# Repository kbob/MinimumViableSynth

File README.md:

# MinimumViableSynth

A virtual analog synthesizer with lots of knobs and buttons.

This is a polyphonic, monotimbral, virtual analog synth.  The audio
engine runs as an Apple Audio Unit on a Macintosh.  The control panel,
shown here, will provide dedicated controls for most of the synth's
functions.

The end goal is a self contained keyboard synth with knobs and buttons
with the classic connections: audio out, MIDI in/out, USB MIDI in/out.
I am getting there in three phases.

  * **Phase 1** (complete 2015-01-01): Softsynth.  The audio engine
    runs as an Audio Unit on a Mac.  It accepts MIDI messages and
    produces beautiful polyphonic analog sounds.  Or gritty,
    disturbing analog sounds.  It plugs in to DAW software (I use
    Logic Pro X).
    
  * **Phase 2** (in progress): Knobs and buttons.  I am designing and
    building a front panel (see above) with knobs, buttons, and an LCD
    touchscreen.  The goal is to make it as easy as possible to
    understand what the synth is doing at any time.

  * **Phase 3** (future): Stand-alone.  Build an enclosure that houses
    a keyboard, the knob and button panel, I/O jacks, and a processor
    (TBD) that can run the audio engine.  I'm looking at FPGAs...

## Why?

Learn stuff.  Music theory, DSP, PCB layout, CAD and machining, more.

## Status

Check out synth-notes.txt for my thoughts as I worked things out.

#### January 7, 2017:

I built 8 slave modules: the LFOs, the Controllers module, the
oscillators, the noise source, mixer, and filter.  I've since killed
the filter module, and one of the oscillators' LED has burnt out its
red component.  I have parts and tools to repair those; just haven't
done it yet.

I have working UI for the knobs and buttons.  Specifically, routing
between modulators and targets works, complete with lighting effects.

I made an enclosure from aluminum sheet and melamine end blocks, as
illustrated above.  It is flimsy, though, so that needs to be re-done.

I had the master, slaves, and LCD panel connected via a breadboard.
The breadboard wiring got flaky, so I stopped to design a PCB.  The
PCB snaps onto the back of the Discovery board, It routes video to the
LCD touch screen, SPI to the slaves, and serial MIDI to a future MIDI
I/O board.

I am currently designing the graphics for the LCD panel.

(Over a year since the last update.  Oops.)

#### December 17, 2015:

Three slave modules have been built.  (LFO1, LFO2, Controllers.)  All
the slave module PCBs are fabricated.

The master-slave communications are working over SPI.  The master
generates MIDI events.
[I can push a button on a slave and hear its effect on the audio
engine.](https://www.youtube.com/watch?v=dZsXk2Zf6Bg)

I blew up one of the LFO modules, probably with static discharge.  I
repaired it (swapped in a new Teensy LC), and it works now.  It was an
ugly repair.

Current tasks:

  + generating more MIDI events
  + experimenting with the LED animation
  + soldering up the rest of the slave modules
  + designing backing plates for the new slave modules

#### August 14, 2015:

The audio engine has been stable since January, though it does not
exactly match the front panel's feature set.

The front panel was fabricated in July.  I used a sheet of acrylic,
painted the underside black, then engraved the artwork through the
paint with a laser cutter.  Then the same laser cutter cut all the
holes for the controls.  It looks sharp, but not mass produced.
I got the work done at [InHaus Fabrication](http://inhausfabrication.com/).

There is a master microcontroller, an STM32F429, and each module has a
slave controller, a Teensy-LC.  Each slave directly drives a few
knobs, buttons, and LEDs.  The master will coordinate all the slaves
and provide the MIDI over USB interface.  I am currently writing SPI
drivers for master-slave communication.

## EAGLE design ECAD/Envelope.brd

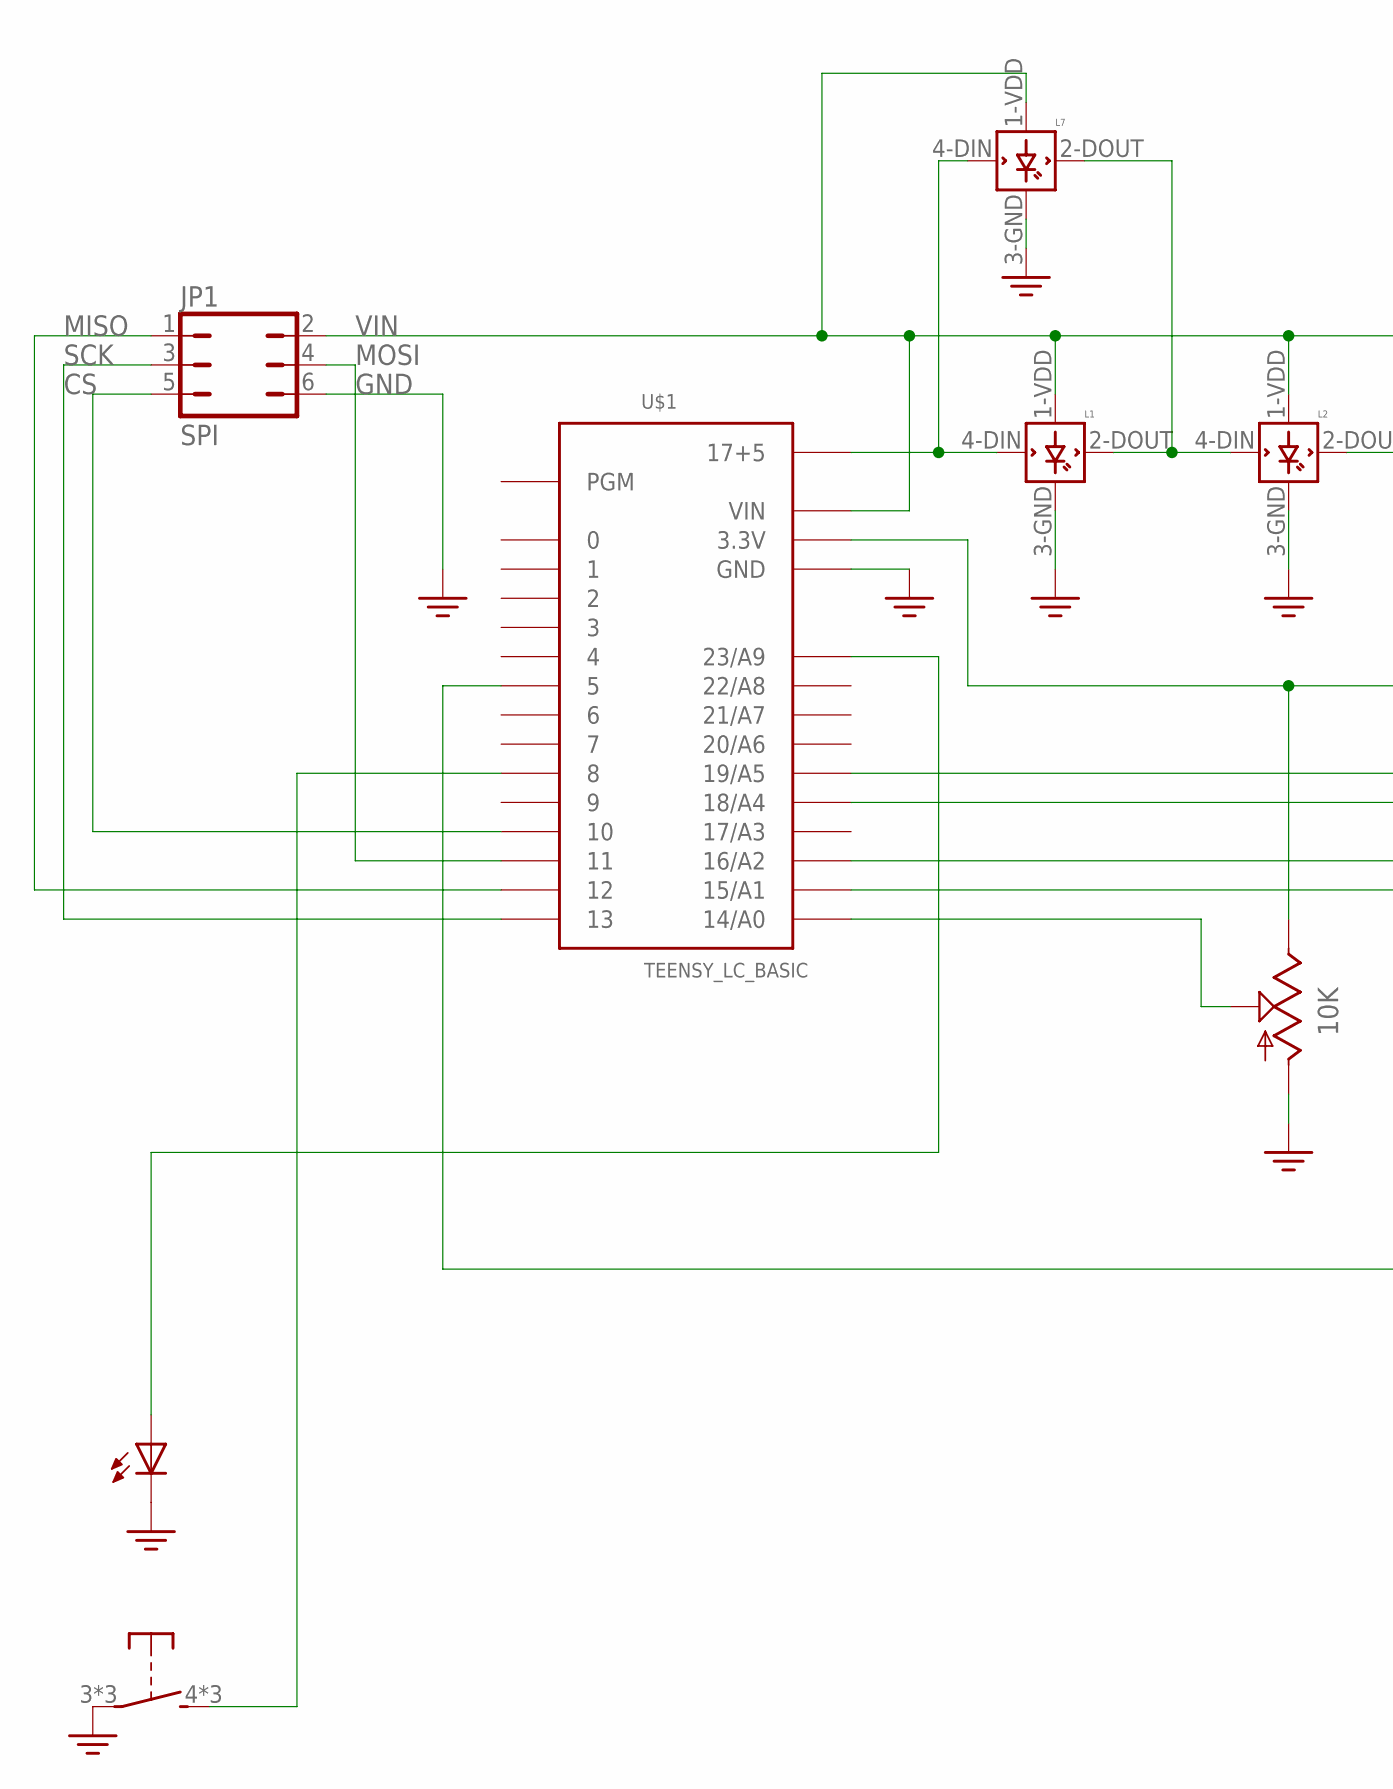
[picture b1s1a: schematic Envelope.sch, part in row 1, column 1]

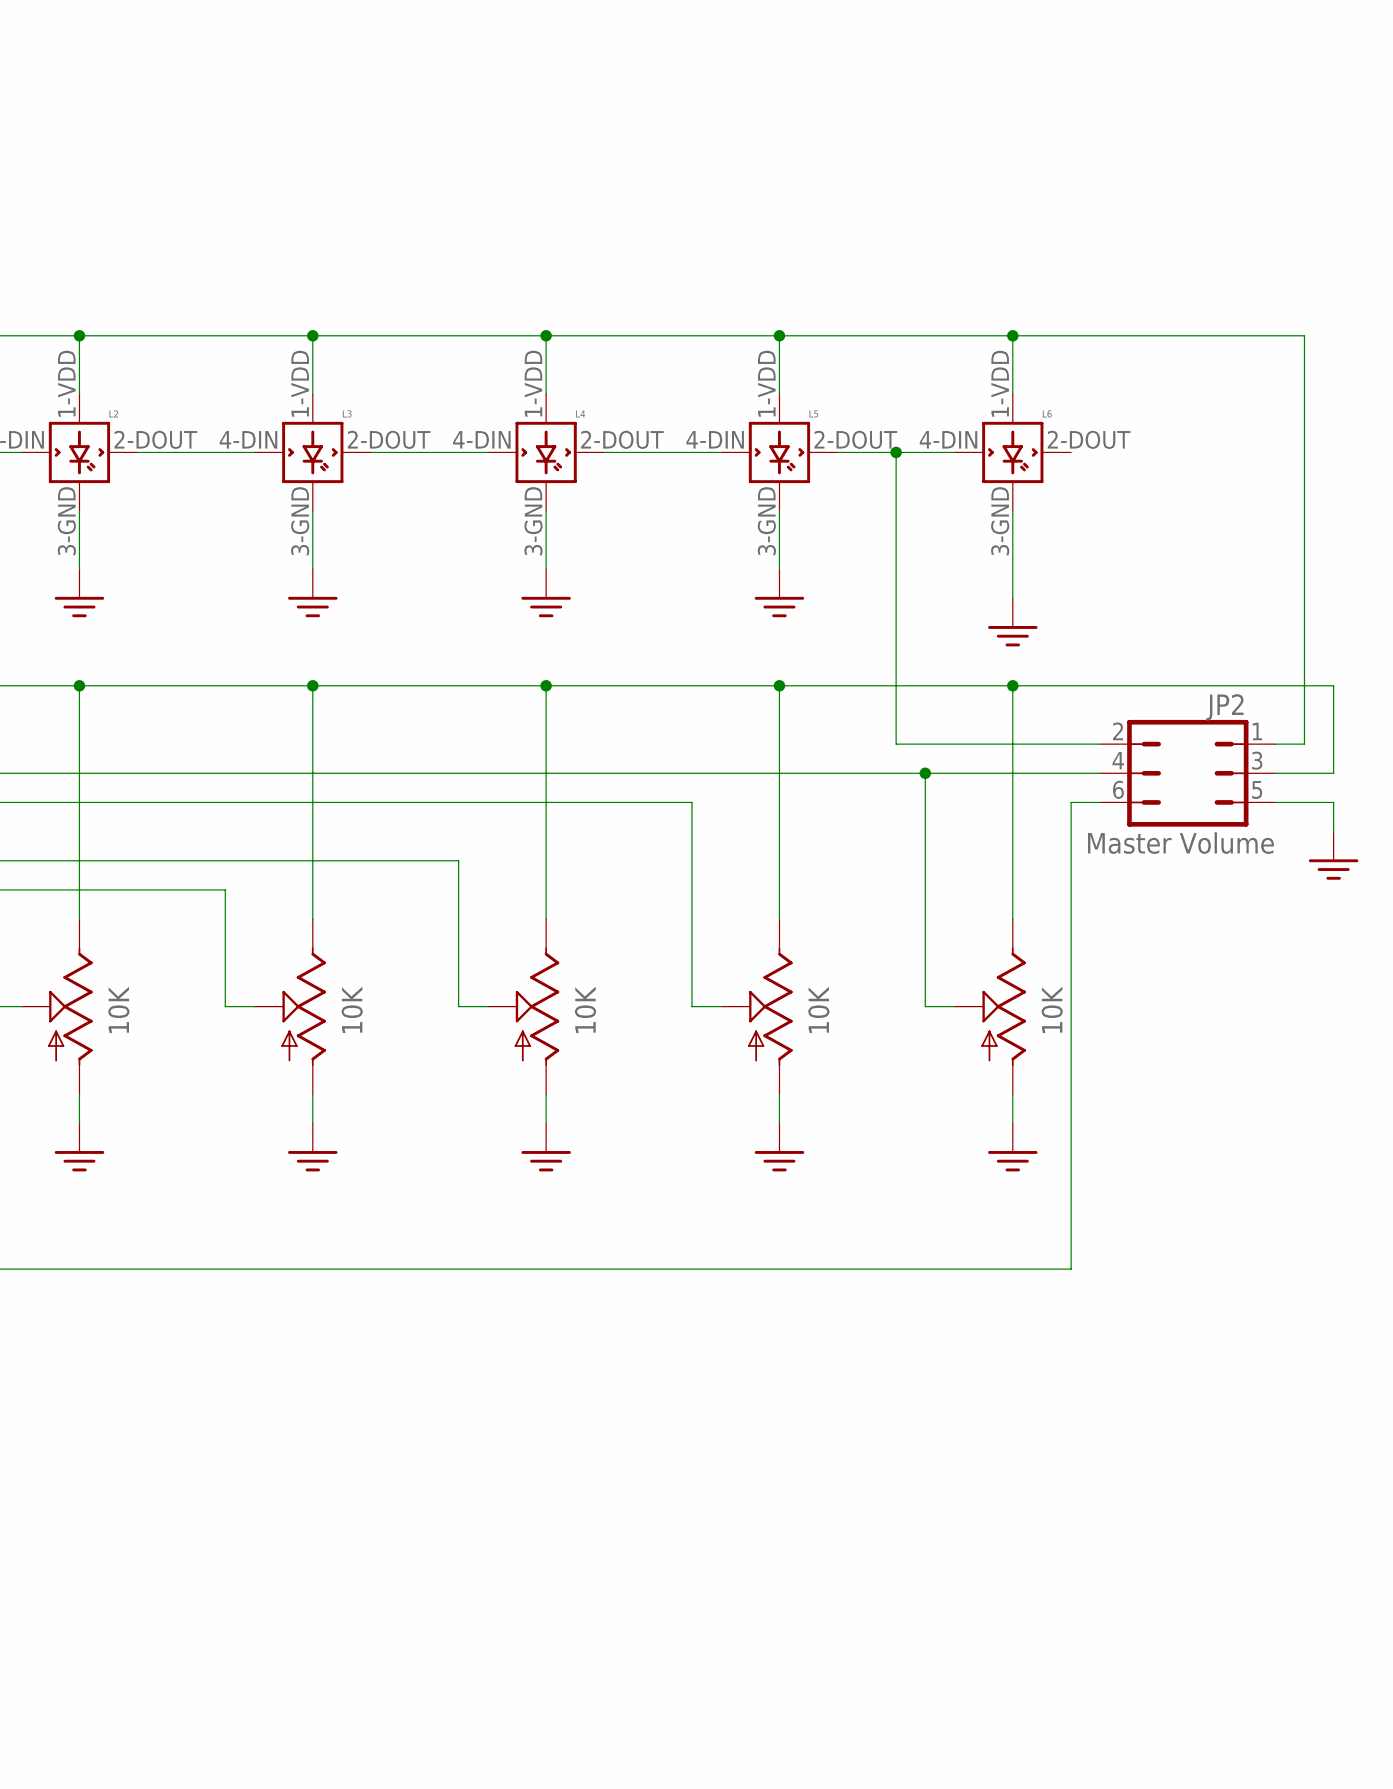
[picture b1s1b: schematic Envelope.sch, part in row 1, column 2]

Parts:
JP1: SPI; JP3Q
JP2: Master Volume; JP3Q
L1, L2, L3, L4, L5, L6, L7: WS2812B
U$1: TEENSY_LC_BASIC
U$2, U$3, U$4, U$5, U$6: 10K; 14MMPOT
U$7: TL1220MEZZ; MEZZ

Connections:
3.3V: JP2.3, U$1.3.3V1 (3.3V), U$2.P$4 (E), U$3.P$4 (E), U$4.P$4 (E), U$5.P$4 (E), U$6.P$4 (E)
GND: JP1.6, JP2.5, L1.3-GND (GND), L2.3-GND (GND), L3.3-GND (GND), L4.3-GND (GND), L5.3-GND (GND), L6.3-GND (GND), L7.3-GND (GND), U$1.GND, U$1.GND1 (GND), U$1.GND2 (GND), U$2.P$5 (A), U$3.P$5 (A), U$4.P$5 (A), U$5.P$5 (A), U$6.P$5 (A), U$7.2 (C), U$7.3, U$7.P$1, U$7.P$2, U$7.P$6 (C)
unnamed: L1.4-DIN (DIN), L7.4-DIN (DIN), U$1.17+5
unnamed: L1.2-DOUT (DOUT), L2.4-DIN (DIN), L7.2-DOUT (DOUT)
unnamed: L2.2-DOUT (DOUT), L3.4-DIN (DIN)
unnamed: L3.2-DOUT (DOUT), L4.4-DIN (DIN)
unnamed: L4.2-DOUT (DOUT), L5.4-DIN (DIN)
unnamed: U$1.23/A9, U$7.1 (A), U$7.P$5 (A)
unnamed: U$1.14/A0, U$2.P$3 (S)
unnamed: U$1.15/A1, U$3.P$3 (S)
unnamed: U$1.16/A2, U$4.P$3 (S)
unnamed: U$1.18/A4, U$5.P$3 (S)
unnamed: U$1.8, U$7.4 (S), U$7.P$3 (S), U$7.P$4 (S)
unnamed: JP2.6, U$1.5
unnamed: JP1.1, U$1.12
unnamed: JP1.3, U$1.13
unnamed: JP1.5, U$1.10
unnamed: JP2.2, L5.2-DOUT (DOUT), L6.4-DIN (DIN)
unnamed: JP2.4, U$1.19/A5, U$6.P$3 (S)
unnamed: JP1.4, U$1.11
VIN: JP1.2, JP2.1, L1.1-VDD (VDD), L2.1-VDD (VDD), L3.1-VDD (VDD), L4.1-VDD (VDD), L5.1-VDD (VDD), L6.1-VDD (VDD), L7.1-VDD (VDD), U$1.VIN

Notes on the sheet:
MISO
SCK
VIN
MOSI
GND

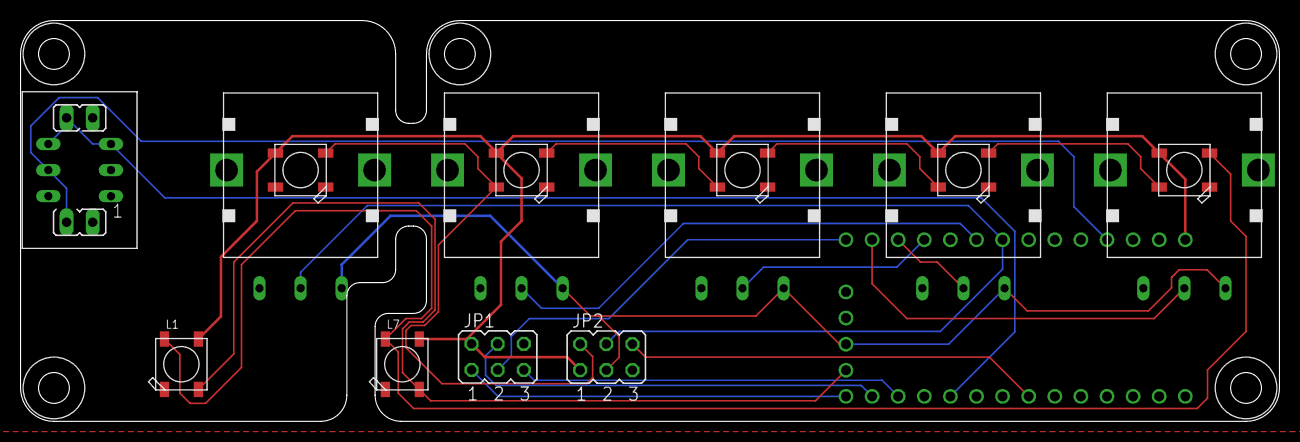
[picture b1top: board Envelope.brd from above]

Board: 2 copper layers, 122.5 x 39.0 mm, 21 parts (1 on the bottom side), 21 nets.

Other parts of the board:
U$8, U$9, U$10, U$11, U$12: STANDOFF-M3

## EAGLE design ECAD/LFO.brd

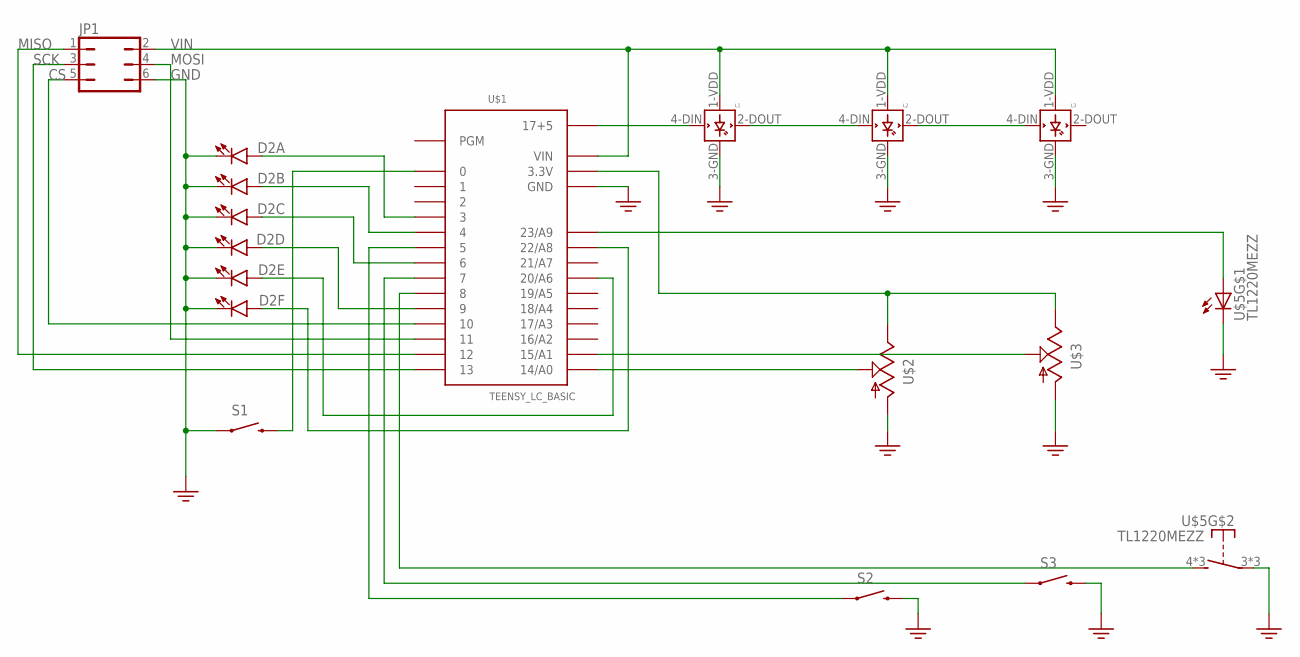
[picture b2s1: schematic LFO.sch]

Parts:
D2: Blue; LED_BARGRAPH_6
JP1: JP1; JP3Q
L1, L2, L3: WS2812B
S1: SWITCH-MOMENTARY-212MM; TACTILE-PTH-12MM
S2, S3: SWITCH-MOMENTARY-2SMD; TACTILE-SWITCH-SMD
U$1: TEENSY_LC_BASIC
U$2, U$3: 10K; 14MMPOT
U$5: TL1220MEZZ; MEZZ

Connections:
3.3V: U$1.3.3V, U$1.3.3V1 (3.3V), U$2.P$4 (E), U$3.P$4 (E)
CS: JP1.5, U$1.10
GND: D2.7 (C), D2.8 (C), D2.9 (C), D2.10 (C), D2.11 (C), D2.12 (C), JP1.6, L1.3-GND (GND), L2.3-GND (GND), L3.3-GND (GND), S1.1, S2.3 (2), S3.3 (2), U$1.GND, U$1.GND1 (GND), U$1.GND2 (GND), U$2.P$5 (A), U$3.P$5 (A), U$5.2 (C), U$5.3, U$5.P$1, U$5.P$2, U$5.P$6 (C)
MISO: JP1.1, U$1.12
MOSI: JP1.4, U$1.11
unnamed: L1.4-DIN (DIN), U$1.17+5
unnamed: L1.2-DOUT (DOUT), L2.4-DIN (DIN)
unnamed: L2.2-DOUT (DOUT), L3.4-DIN (DIN)
unnamed: D2.4 (A), U$1.9
unnamed: D2.5 (A), U$1.20/A6
unnamed: D2.6 (A), U$1.22/A8
unnamed: D2.3 (A), U$1.6
unnamed: D2.1 (A), U$1.3
unnamed: D2.2 (A), U$1.4
unnamed: S1.3 (2), U$1.0
unnamed: U$1.14/A0, U$2.P$3 (S)
unnamed: U$1.15/A1, U$3.P$3 (S)
unnamed: U$1.8, U$5.4 (S), U$5.P$3 (S), U$5.P$4 (S)
unnamed: S3.1, U$1.7
unnamed: U$1.23/A9, U$5.1 (A), U$5.P$5 (A)
unnamed: S2.1, U$1.5
SCK: JP1.3, U$1.13
VIN: JP1.2, L1.1-VDD (VDD), L2.1-VDD (VDD), L3.1-VDD (VDD), U$1.VIN

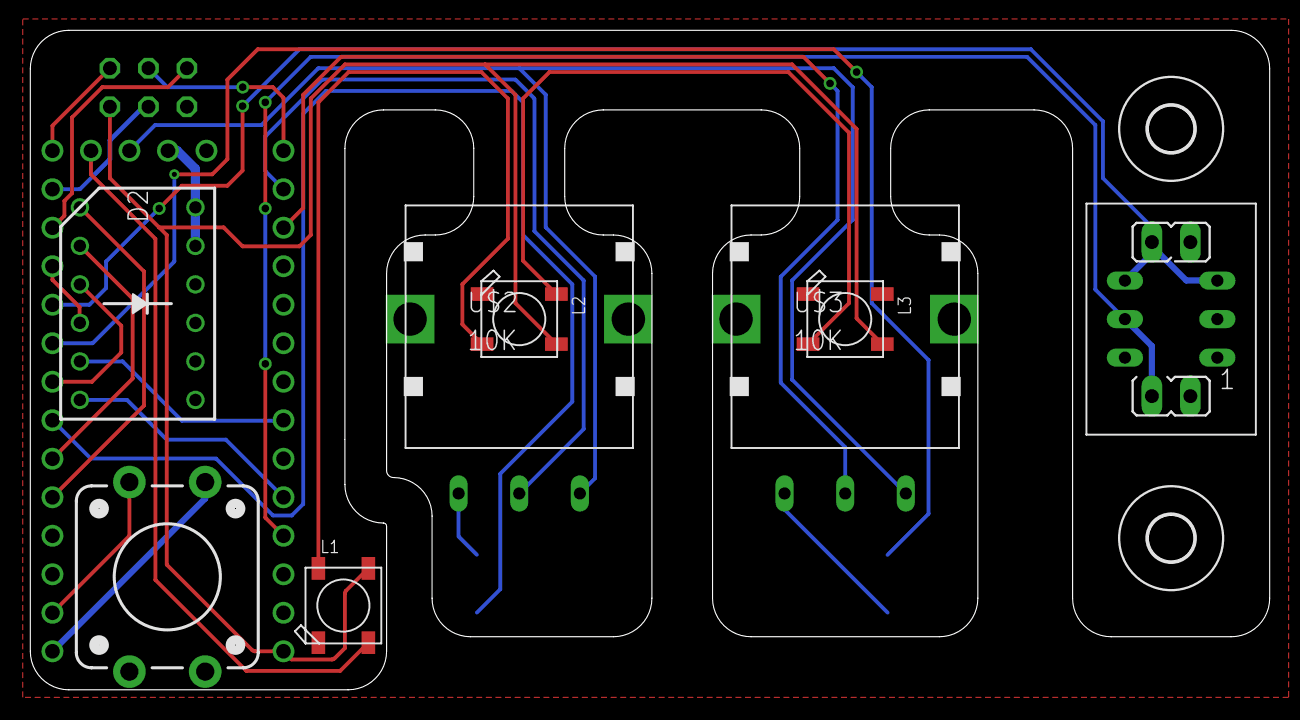
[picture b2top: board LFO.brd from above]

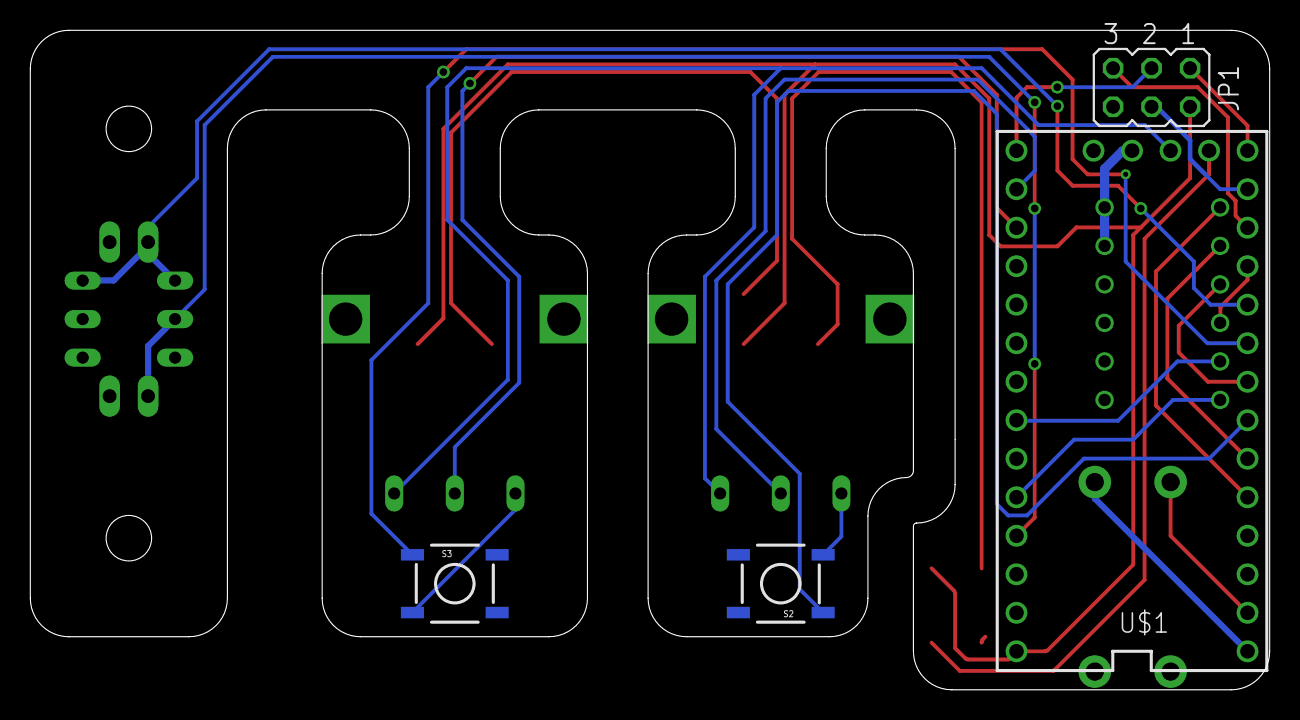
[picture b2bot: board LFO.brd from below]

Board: 2 copper layers, 81.8 x 43.5 mm, 14 parts (4 on the bottom side), 23 nets.

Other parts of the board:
U$4, U$6: 3,0

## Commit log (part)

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2014-11-19 Minimum Viable Synth. Mostly works. Some parameters' scales are wrong.
2014-11-19 Implement velocity, fixup parameters.
2014-11-19 Still just cosmetic. Indentation, comments, removed unused method MVS::GetControls().
2014-11-20 More cleanup. Removed DEBUG_PRINT, removed no-op MVSNote::Kill() method, cleaned up MVSNote::Render().
2014-11-22 Globally renamed MVS to MVS 2. Now has sine, sawtooth, triangle, square, and pulse waveforms with continuous waveform modulation under MIDI control.
2014-11-29 Increased maximum number of voices to 18.
2014-11-29 Now ⌘-B create Release build. Needed so the decimation filter will vectorize.
2014-11-29 Now the synth runs with 4× oversampling.
2014-11-29 Enabled Triangle waveform. Changed direction of triangle skew to match sawtooth.
2014-11-29 Removed zipper noise when quickly modulating square wave pulse width.
2014-11-30 Increased max polyphony to 500. Changed ADSR time parameters to allow range of 0 .. 10 seconds with cube root display.
2014-12-01 Implemented exponential envelopes. Now uses exponential envelope for note amplitude.
2014-12-04 Now has two oscillators.
2014-12-10 Separated Oscillator 2's detune parameter into coarse and fine parts.
2014-12-15 Renamed MVS 3 to MVS 4.
2014-12-15 Silenced all compiler warnings.
2014-12-19 New parameter infrastructure. Removed vibrato and noise envelope. Needs much cleanup, but checking now because it's in a working state.
2014-12-19 Much cleanup. Removed dead code from old parameter infrastructure.
2014-12-20 Commented out a lot of unimplemented parameters. Renamed Oscillator::Type to Oscillator::Waveform.
2014-12-20 New ModWheel module gives smoothed Modulation Wheel data. Plumbing to get modulation to MVSNotes.
2014-12-21 Interim version. Working toward a full modulation matrix.
2014-12-24 Modulation matrix implemented. Changing a destination parameter updates the modulation matrix.
2014-12-25 Modulation matrix mostly implemented. Modulation sources ModWheel, LFO1, LFO2, several destinations. Also implemented ring modulator and hard sync.
2014-12-30 Now you can turn the (nonexistent) filter off, and Osc 2 detune has been adjusted to work better with the range of MIDI controllers (0..127).
2014-12-31 Tweaked parameter limits to play better with AU Lab's MIDI interface. I think AU Lab is wrong, but I'll conform anyway.
2015-01-01 New envelopes. Parameters are fully modulable. Also new Amplifier component -- the former AmpEnv has been decomposed.
2015-01-01 Finished renaming Modwheel files to ModWheel.
2015-01-01 Added comments to delineate the sections in MVSParamSet::MVSParamSet().
2015-01-01 Fixed Envelope 2 amount control.
2015-01-02 Ring Modulator volume now depends only on Oscillator 1 volume. The other way was too error prone.
2015-01-02 Implemented filter keytracking.
2015-01-02 Implemented key tracking for Envelope 2.
2015-01-04 Now restores user presets.
2015-01-04 Now has a factory preset.
2015-01-10 Continued tweaking parameters, now passes AU validation.
2015-01-12 AU Lab bug compatibility is now wrapped in AULAB_BUG_COMPAT. When undefined, synth works with Logic Pro X.
2015-01-15 Created a separate build target for the Logic Pro version.
2015-01-15 Added new target: MVS 4 - AU Lab.
2015-05-29 Moved audio units into the Audio Unit subdirectory.
2015-05-29 Imported Eagle CAD files. They probably don't build in this environment.
2015-05-29 Checked in the LFO substrate mechanical CAD drawing.
2015-05-30 synth-dsl.py generates the front panel.
2015-05-31 Removed some unneeded switch devices, added a SPI jumper (unfinished).
2015-05-31 Everything.sch - a template module schematic with the union of all circuits
2015-05-31 synth-notes.txt - I've been taking notes for the last 8 months.
2015-05-31 embiggen-filter.py - rewrite filter.brd to actual size, since the Eagle file is compressed.
2015-05-31 Aaaauurghh! Misspelled "Minimum Viable Synth"!
2015-05-31 Fixed a skewed wire.
2015-05-31 Two more PCBs: Oscillator and Duo (the two-control board).
2015-05-31 ... still renaming "LFO Small" to "LFO".
2015-05-31 Moved the LED bar graphs' color labels to the silkscreen layer.
2015-05-31 ... testing on repo ...
2015-05-31 Ignore emacs temp files.
2015-05-31 Starting to design the envelope control boards
2015-05-31 This is the filter board, with the controls spaced out to the right positions.
2015-05-31 Added brief description and status.
2015-05-31 misc. updates
2015-05-31 1.0 versions of the Filter, Oscillator, and Duo boards sent to OSHPark and archived.
2015-06-01 Designed the Envelope board. Fairly straightforward, except that it has three variants.
2015-06-01 Envelope and Master Volume 1.0 archived and sent to fab.
2015-06-01 LFO substrate: more clearance around SPI header, single top clip, strain relief in spine.
2015-06-09 Changed based on Kris@inhausfabrication.com's suggestions
2015-06-09 Initial checkin of master firmware. USB MIDI works, SPI works.
2015-06-09 Documented the protocol between master and slave.
2015-06-09 Archive copies of files sent for laser cutting
2015-06-11 Changes based on first lasercut prototypes. More coming.
2015-06-11 Made the envelope filter destination arrow swoopy.
2015-06-15 Added cmd line args to select the different output modes.
2015-06-15 Shell script renders all the different front panel files.
2015-06-15 Archived v0.3 front panel files, as they've been sent to fab.
2015-06-21 Variant LFO substrate is thicker to clear power jumpers.
2015-07-31 Fixed panel size calculation for paginated output.
2015-08-09 Added const declarations where appropriate.
2015-08-09 Master now transmits SPI data using DMA.
2015-08-09 Cleaned up SPI DMA in SPI-master firmware.
2015-08-10 GPIO cleanup.
2015-08-10 Cut over all modules to new GPIO API.
2015-08-17 Now draws module destination arrows in artwork mode.
2015-08-17 Updated README.
2015-08-17 Implemented synth_config and synth_state data structures.
2015-08-17 Checked in the wrong file.
2015-08-20 Just added a comment.
2015-08-20 Made module and knob index symbols public. Created module/knob config flags.
2015-08-20 Started defining factory defaults. Got bogged down thinking about how the Controllers module will work.
2015-08-20 Preliminary thoughts about the Controllers module.
2015-11-26 Unknown changes.
2015-11-26 Now Master sends well-formed messages to Slave(s).
2015-11-30 Slave firmware serial port use is #ifdef'd out.
2015-11-30 Increased system clock to 50 Hz, SPI clock to 600 Hz.
2015-11-30 Fixed stupid bug in Fletcher-16 checksum.
2015-11-30 Now runs at full speed: SPI clock ~5 MHz, system tick 1 msec.
2015-12-02 Moved SPI group B select from pin PA9 to PC13. Conflict on PA9.
2015-12-06 Outlined APIs for MIDI, USB, and SPI drivers.
2015-12-06 MIDI API defined.
2015-12-06 Now draws the modules in color.
2015-12-06 Now SPI DMA interrupts on completion.
2015-12-09 Lots of cleanup.
2015-12-09 Still tweaking the colors.
2015-12-10 Now one button works end to end. Press a Choice button; send a MIDI CC message.
2015-12-10 Button notes use real MIDI API.
2015-12-18 First status update in 4 months.
2015-12-18 Updated front page picture.
2015-12-20 Now prints a helpful message if $LIBOPENCM3 is undefined.
2015-12-21 Updated to XCode 7.2. Fixed bug in enum params > 10 states.
2015-12-22 Designed substrates to hold up several slave boards.
2015-12-22 Added strain relief slots to the filter substrate.
2015-12-22 Assign button is dark when source is unassigned.
2015-12-22 Tweaked clearance for Teensy.
2016-01-17 Started adding datasheets for parts used.
2016-01-17 OpenSCAD animation of how to assemble the parts.
2016-01-17 Re-rendered assembly GIF with perspective view.
2016-01-17 Changed the button to drop every 6th note by 3 octaves.
2016-01-17 Filter has 3 choices, not 6.
2016-01-17 Fixed sequence error with multiple SPI buses active.
2016-01-17 Added code to show back panel jack positions.
2016-01-18 Described enclosure plans.
2016-01-27 Made a plastic plug to fit in the end of the case.
2016-01-27 Sample graphics image and RLE compiler for graphics test.
2016-02-06 Added plate to screw on end cap.
2016-02-06 Keep tweaking geometry until it fits.
2016-02-06 Enable the first eight modules.
2016-02-06 Added LCD-TFT and SDRAM drivers.
2016-02-06 Added speed and type to gpio pins, cleaned up gpio pin init.
2016-02-07 Clean up GPIO init.
2016-02-10 Changed group B slave select again to PE3.
2016-02-10 Ugh.
2016-02-11 Removed dead code from lcd-dma.c.
2016-02-11 Slave self-test no longer leaves extra choice LEDs on.
2016-02-17 Conditioned analog inputs to avoid spurious movement.
2016-02-17 Recorded issues fixed.
2016-02-22 Fixed LCD-TFT startup.
2016-03-25 Re-enabled printing bad packets.
2016-03-25 Added statistics to USB-MIDI.
2016-03-25 Created WITH_INTERRUPTS_MASKED module.
2016-03-25 Removed junk.
2016-08-17 Now compiles both binary and include files formats.
2016-11-08 New synth notes. Starting to plan out I/O daughtercard.
2016-11-09 Moved module PCBs to ECAD/modules/.
2016-11-10 Started I/O Daughter Board. Collected data sheets.
2016-11-11 Major components are in the schematic.
2016-11-12 annotated the P1 connector.
2016-11-12 Tweaked P1 pins 1-16.
2016-11-12 Annotated P2 pins.
2016-11-13 Preliminary notes on the MIDI board.
2016-11-13 Capacitive touch connector.
2016-11-14 Should not have committed backup file.
2016-11-14 Schematic for backlight power supply drawn.
2016-11-14 added slave connectors to schematic; laid out page.
2016-11-14 More schematic tweaks.
2016-11-16 Fixed 10 errors on schematic. Still no power flags.
2016-11-16 spello.
2016-11-16 Schematic annotated and electrical rules checked.
2016-11-16 Added footprints for the easy components.
2016-11-18 Drew and dimensioned board outline.
2016-11-18 Flipped board to make LCD right side up. Regenerated netlist with footprints.
2016-11-18 git ignore *-rescue.lib.
2016-11-18 Changed values of slave connectors to "Slave 1A" etc.
2016-11-21 P1 and P2 connectors placed. Back to PicoBlade through-hole connectors.
2016-11-21 Placed J1 and J2 FPC connectors.
2016-11-21 Ignore KiCad .rpt files.
2016-11-22 All components are on the board.
2016-11-22 Ready to autoroute?
2016-11-22 Repositioned RTOUCH circuit.
2016-11-23 Try moving the SPI buffers around. Manually route bypass caps.
2016-11-23 Moved reset button resistors.
2016-11-23 Freerouting rules and configuration.
2016-11-23 Board autorouted, DRC and missing connections fixed.
2016-11-25 Working on BOM.
2016-11-27 Re-autorouted with no ground plane.
2016-11-27 Cleaned up silkscreen.
2016-11-28 Added logo to back of board.
2016-11-29 Widened ground traces failed DRC.
2016-11-29 The footprint for the no-solder resistor
2016-11-29 Switched connectors P1 and P2. Made traces for filter caps.
2016-11-29 Re-routed board with P1/P2 corrected, added explicit ground-to-bypass traces.
2016-11-29 Added ground plane; widened ground traces to slave connectors.
2016-11-29 Improved ground plane around slave connectors.
2016-12-17 Created stuffing guide.
2016-12-17 Updated datasheets.
2016-12-17 Removed all traces and vias (again).
2016-12-17 Changed solder mask clearance to 0.05 mm. (Grrr!)
2016-12-17 Changed LCD connector to Hirose FH12A.
2016-12-18 Fixed arrowhead.
2016-12-18 Routed board. Same as always - no ground pour, three trace sizes.
2016-12-18 Typo in comment.
2016-12-19 Changed barrel jack hole sizes to 1.1mm.
2016-12-19 Disconnected +3.3V from P2.
2016-12-19 Removed all traces and copper pours; reconnected filter caps.
2016-12-19 git ignore *.kicad_pcb.orig files.
2016-12-20 Added copper pours front and back for ground.
2017-01-06 Video works with I/O daughterboard and 5" LCD-TFT screen.
